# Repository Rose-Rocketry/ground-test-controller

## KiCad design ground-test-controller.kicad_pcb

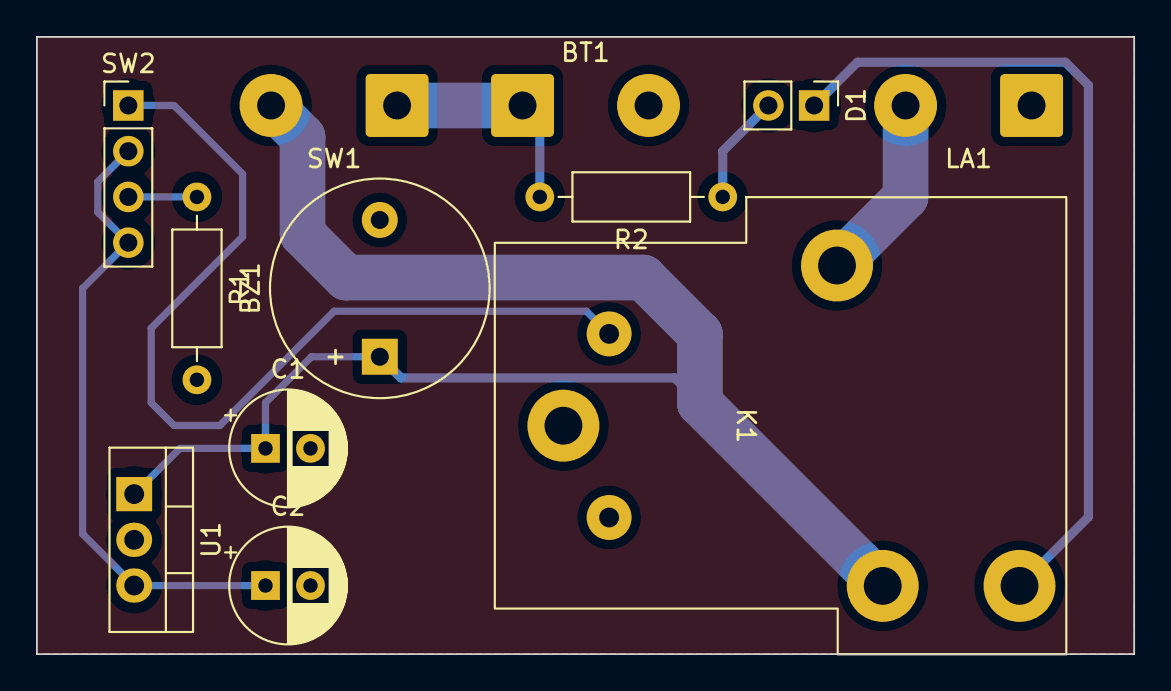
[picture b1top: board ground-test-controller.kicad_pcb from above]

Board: 2 copper layers, 61.0 x 34.3 mm, 12 parts (0 on the bottom side), 9 nets.

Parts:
BT1: Battery; SolderWire-0.75sqmm_1x02_P7mm_D1.25mm_OD3.5mm
BZ1: Buzzer; Buzzer_12x9.5RM7.6
C1, C2: 10uF; CP_Radial_D6.3mm_P2.50mm
D1: Orange; PinHeader_1x02_P2.54mm_Vertical
K1: PR23-xV-900-1C
LA1: Igniter; SolderWire-0.75sqmm_1x02_P7mm_D1.25mm_OD3.5mm
R1: 220; R_Axial_DIN0207_L6.3mm_D2.5mm_P10.16mm_Horizontal
R2: 510; R_Axial_DIN0207_L6.3mm_D2.5mm_P10.16mm_Horizontal
SW1: SW_SPST; SolderWire-0.75sqmm_1x02_P7mm_D1.25mm_OD3.5mm
SW2: SW_Push_LED; PinHeader_1x04_P2.54mm_Vertical
U1: LM7805_TO220; TO-220-3_Vertical

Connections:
+5V: C2.1, SW2.2, SW2.4 (A), U1.3 (VO)
+BATT: BT1.1 (+), R2.2, SW1.1 (A)
/ALED: R1.1, SW2.3 (K)
/COIL: K1.2, SW2.1
/OUT: K1.4, LA1.2 (+)
/TEST: D1.1 (K), K1.5
/TLED: D1.2 (A), R2.1
/VSW: BZ1.1 (-), C1.1, K1.6, SW1.2 (B), U1.1 (VI)
GND: BT1.2 (-), BZ1.2 (+), C1.2, C2.2, K1.1, LA1.1 (-), R1.2, U1.2 (GND)

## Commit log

2024-11-19 Initial upload of PCB files
